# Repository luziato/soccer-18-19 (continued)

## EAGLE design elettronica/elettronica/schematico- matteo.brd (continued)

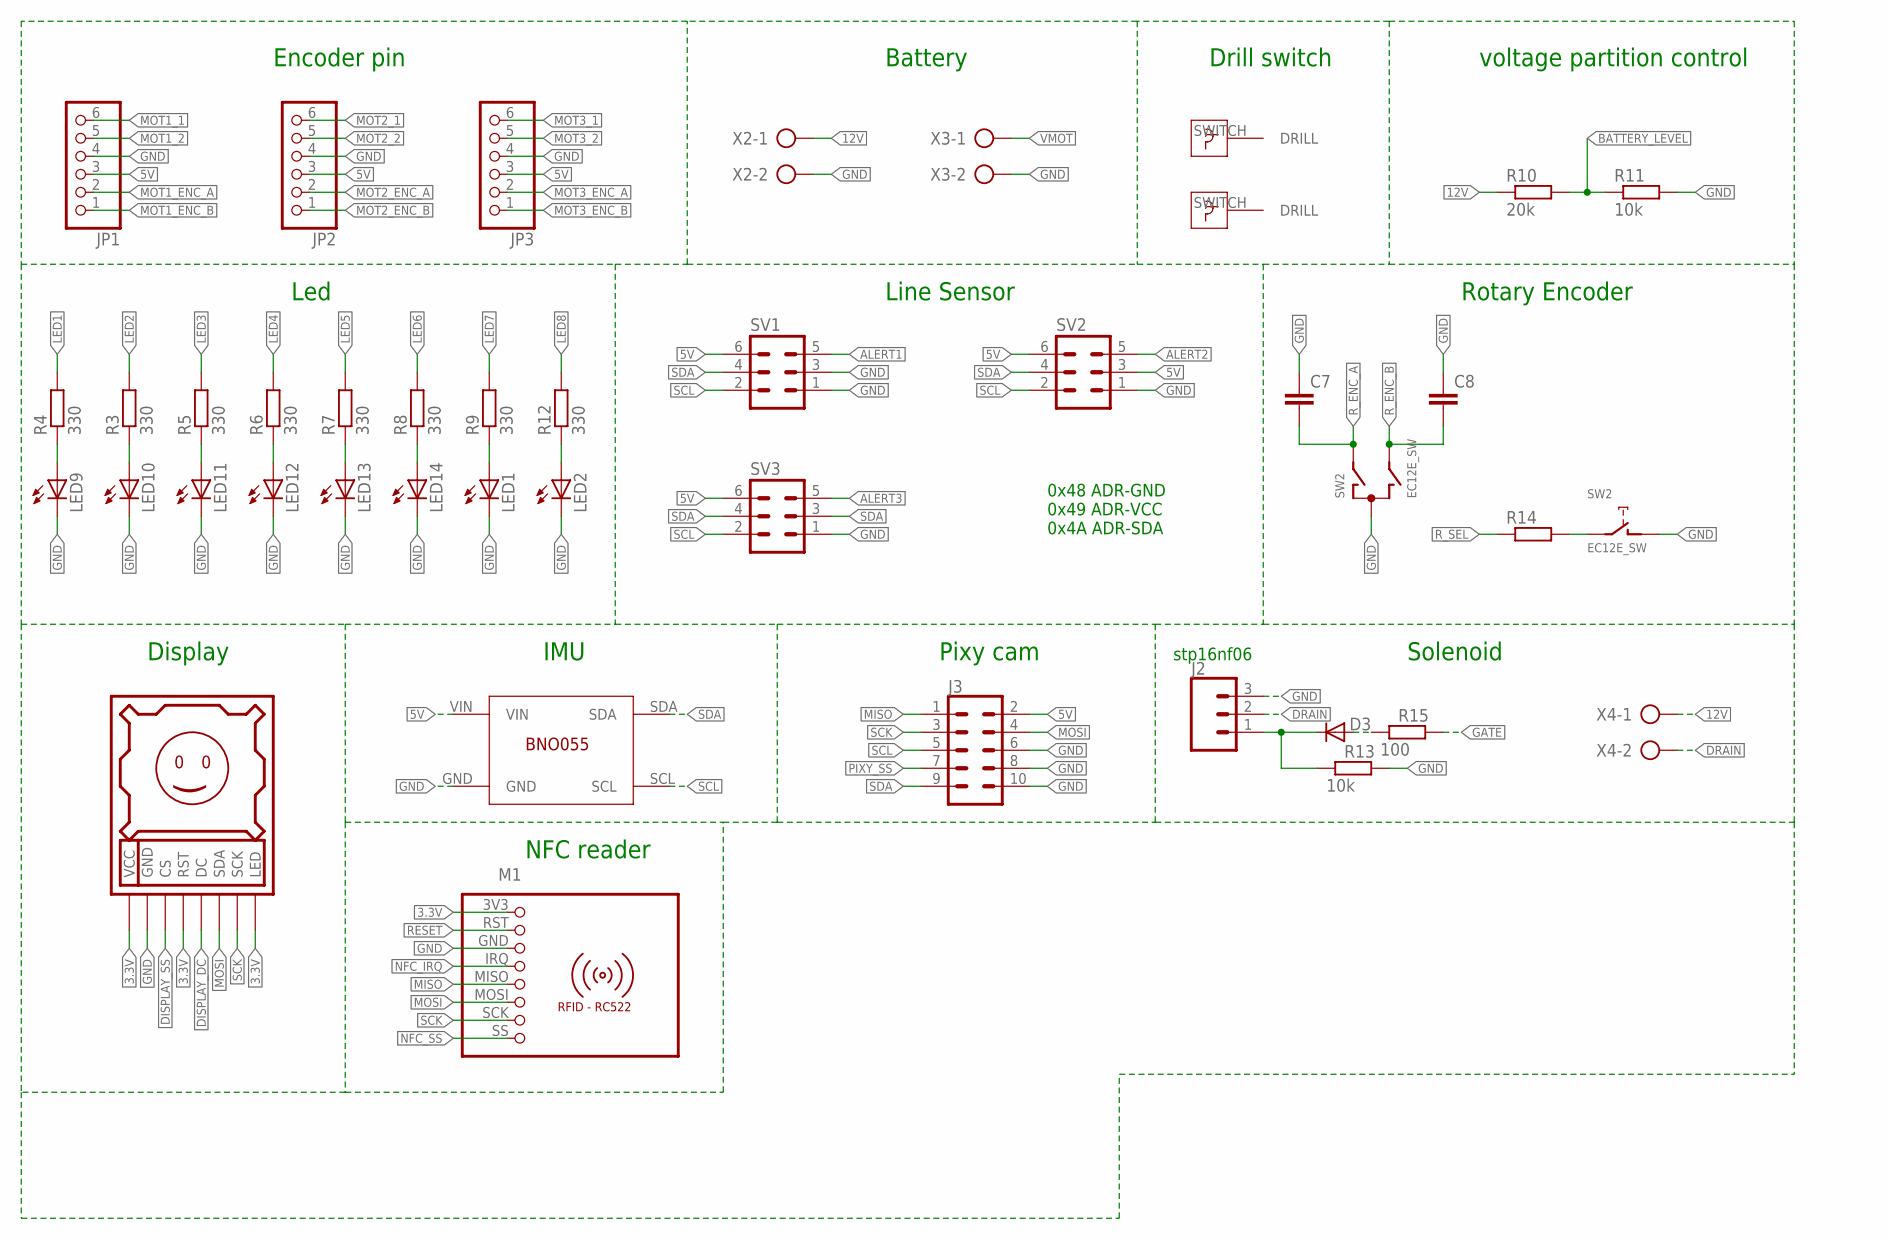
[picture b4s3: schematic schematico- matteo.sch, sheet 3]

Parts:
C7, C8: C-EUC1206; C1206
D3: 1N4148; DO35-7
DISPLAY1: DISPLAY128X128
J2: 455-1750-1-ND; 1X03
J3: CONN_05X2PTH; 2X5
JP1, JP2, JP3: PINHD-1X6; 1X06
LED1, LED2, LED9, LED10, LED11, LED12, LED13, LED14: TLLG4400; LED3MM
M1: RFID-RC522
R3, R4, R5, R6, R7, R8, R9, R12: 330; R1206
R10: 20k; 0204/7
R11: 10k; 0204/7
R13: 10k; R1206
R14: R-EU_M1206; M1206
R15: 100; R1206
SV1, SV2, SV3: MA03-2
SW2: EC12E_SW; ALPS_EC12E_SW
U$12, U$13: DRILL_SWITCH
U$15: BNO055; BNO005
X2, X3, X4: AK500/2-H

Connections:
3.3V: DISPLAY1.LED, DISPLAY1.RST, DISPLAY1.VCC, M1.3V3 (1); also elsewhere on the board
5V: J3.2, JP1.3, JP2.3, JP3.3, SV1.6, SV2.3, SV2.6, SV3.6, U$15.VIN; also elsewhere on the board
12V: R10.1, X2.1, X4.1; also elsewhere on the board
ALERT1: SV1.5; also elsewhere on the board
ALERT2: SV2.5; also elsewhere on the board
ALERT3: SV3.5; also elsewhere on the board
BATTERY_LEVEL: R10.2, R11.1; also elsewhere on the board
DISPLAY_DC: DISPLAY1.DC; also elsewhere on the board
DISPLAY_SS: DISPLAY1.CS; also elsewhere on the board
DRAIN: J2.2, X4.2
GATE: R15.2; also elsewhere on the board
GND: C7.1, C8.1, DISPLAY1.GND, J2.3, J3.6, J3.8, J3.10, JP1.4, JP2.4, JP3.4, LED1.K (C), LED2.K (C), LED9.K (C), LED10.K (C), LED11.K (C), LED12.K (C), LED13.K (C), LED14.K (C), M1.GND (3), R11.2, R13.2, SV1.1, SV1.3, SV2.1, SV3.1, SW2.C, SW2.D (1), U$15.GND, X2.2, X3.2; also elsewhere on the board
LED1: R4.2; also elsewhere on the board
LED2: R3.2; also elsewhere on the board
LED3: R5.2; also elsewhere on the board
LED4: R6.2; also elsewhere on the board
LED5: R7.2; also elsewhere on the board
LED6: R8.2; also elsewhere on the board
LED7: R9.2; also elsewhere on the board
LED8: R12.2; also elsewhere on the board
MISO: J3.1, M1.MISO (5); also elsewhere on the board
MOSI: DISPLAY1.SDA, J3.4, M1.MOSI (6); also elsewhere on the board
MOT1_1: JP1.6; also elsewhere on the board
MOT1_2: JP1.5; also elsewhere on the board
MOT1_ENC_A: JP1.2; also elsewhere on the board
MOT1_ENC_B: JP1.1; also elsewhere on the board
MOT2_1: JP2.6; also elsewhere on the board
MOT2_2: JP2.5; also elsewhere on the board
MOT2_ENC_A: JP2.2; also elsewhere on the board
MOT2_ENC_B: JP2.1; also elsewhere on the board
MOT3_1: JP3.6; also elsewhere on the board
MOT3_2: JP3.5; also elsewhere on the board
MOT3_ENC_A: JP3.2; also elsewhere on the board
MOT3_ENC_B: JP3.1; also elsewhere on the board
unnamed: LED9.A, R4.1
unnamed: LED10.A, R3.1
unnamed: LED11.A, R5.1
unnamed: LED12.A, R6.1
unnamed: LED13.A, R7.1
unnamed: LED14.A, R8.1
unnamed: D3.C, J2.1, R13.1
unnamed: D3.A, R15.1
unnamed: LED1.A, R9.1
unnamed: LED2.A, R12.1
unnamed: R14.2, SW2.E (2)
NFC_IRQ: M1.IRQ (4); also elsewhere on the board
NFC_SS: M1.SS (8); also elsewhere on the board
PIXY_SS: J3.7; also elsewhere on the board
RESET: M1.RST (2); also elsewhere on the board
R_ENC_A: C7.2, SW2.A; also elsewhere on the board
R_ENC_B: C8.2, SW2.B; also elsewhere on the board
R_SEL: R14.1; also elsewhere on the board
SCK: DISPLAY1.SCK, J3.3, M1.SCK (7); also elsewhere on the board
SCL: J3.5, SV1.2, SV2.2, SV3.2, U$15.SCL; also elsewhere on the board
SDA: J3.9, SV1.4, SV2.4, SV3.3, SV3.4, U$15.SDA; also elsewhere on the board
VMOT: X3.1; also elsewhere on the board

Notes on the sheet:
Encoder pin
Battery
Drill switch
Led
0x48 ADR-GND 0x49 ADR-VCC 0x4A ADR-SDA
voltage partition control
Rotary Encoder
Line Sensor
Display
Solenoid
IMU
Pixy cam
NFC reader
stp16nf06

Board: 2 copper layers, 93 parts (0 on the bottom side), 100 nets, no tracks yet.

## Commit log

2018-12-26 ok mi sembra tutto
2018-12-26 no così
2019-01-11 compiti vacanze
2019-01-11 corretto
2019-01-12 Phoenix_line e Phoenix_line_internals
    .h & .cpp
2019-01-15 Elettronica
2019-01-16 bla bla
2019-01-17 compilato correttamente
2019-01-21 aggiunta la motor hub
2019-01-22 posizionare i pezzi nella board
    aggiute anche ulp per autoposizionamento e drc sparkfun
2019-01-23 continuare a posizionare i pezzi nella board
2019-01-24 tutto compila perfettamente ora è da provare
2019-01-24 funziona tutto
2019-01-31 PCB Finita
    posizionati tutti i componenti e tracciate tutte le piste
2019-01-31 PCB DEFINITIVA
2019-02-05 sensori di linea done
2019-02-07 pcb definitiva 2.0
2019-02-13 adding vector graphic
2019-03-17 dovrebbe essere tutto
2019-03-18 sistemati gli encoder
2019-03-18 ok tutto corretto
2019-03-21 proviamo tutto
2019-03-23 matrice inversa e matrice ancora da provare, pixy sistemata
2019-03-29 yatili e steora funzionano
    mancano sensori di linea
    da migliorare pid
2019-03-29 compitato tutto funziona in teoria
2019-03-31 Un po'di roba da provare e sistemare
    tra cui il PID e alcune funzioni in firmware
2019-04-02 mancano i sensori di linea
2019-04-02 primo giorno di gare un po' di modifiche soprattutto ai sensori di linea
2019-04-03 DOVREBBE
2019-04-08 post gare
2019-04-13 Trigger di Schmitt e contatore
